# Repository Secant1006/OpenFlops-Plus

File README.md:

# OpenFlops-Plus
Enhanced version of open-source gotek

[OpenFlops](https://github.com/SukkoPera/OpenFlops)

[FlashFloppy](https://github.com/keirf/flashfloppy)

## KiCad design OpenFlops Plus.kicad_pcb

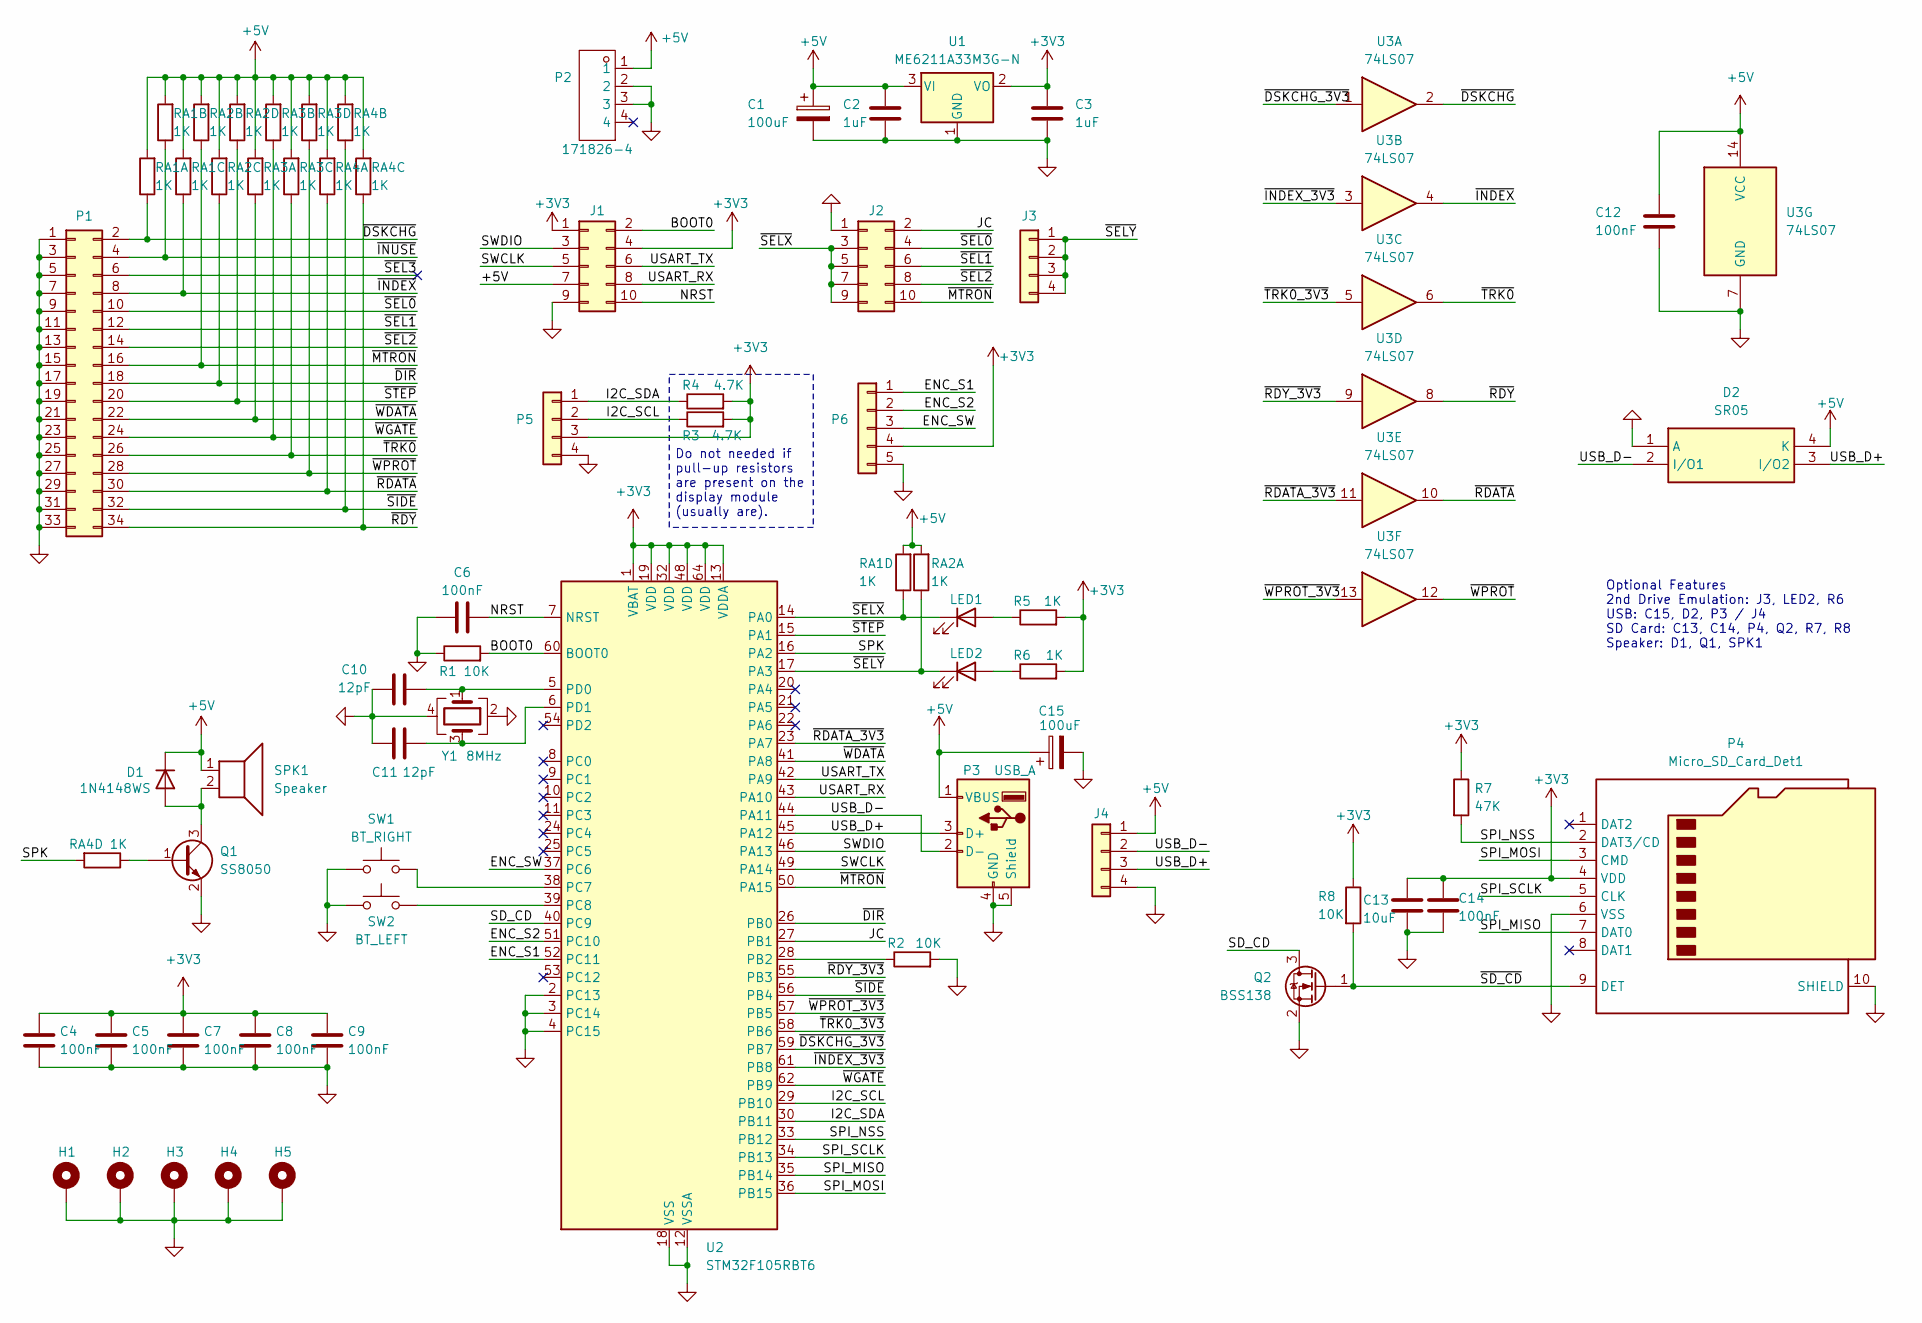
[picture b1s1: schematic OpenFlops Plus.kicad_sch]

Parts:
C1, C15: 100uF; CP_Radial_D6.3mm_P2.50mm
C2, C3: 1uF; C_0603_1608Metric
C4, C5, C6, C7, C8, C9, C12, C14: 100nF; C_0603_1608Metric
C10, C11: 12pF; C_0603_1608Metric
C13: 10uF; C_0805_2012Metric
D1: 1N4148WS; D_SOD-323
D2: SR05; SOT-143; Manufacturer_Part_Number SR05.TCT; Mouser Part Number 947-SR05.TCT
H1, H2, H3, H4, H5: MountingHole_Pad; MountingHole_3.2mm_M3_Pad
J1, J2: Conn_02x05_Odd_Even; PinHeader_2x05_P2.54mm_Vertical
J3, J4: Conn_01x04; PinHeader_1x04_P2.54mm_Vertical
LED1, LED2: LED; LED_D3.0mm
P1: Conn_02x17_Odd_Even; PinHeader_2x17_P2.54mm_Vertical
P2: 171826-4; CONN-TH_4P-P2.50_171826-4; Manufacturer Part 171826-4; LCSC Part Name 1x4P 间距:2.5mm 弯插
P3: USB_A; USB_A_Molex_67643_Horizontal
P4: Micro_SD_Card_Det1; TF-SMD_XKTF-015-N
P5: Conn_01x04; PinHeader_1x04_P2.54mm_Vertical
P6: Conn_01x05; PinHeader_1x05_P2.54mm_Vertical
Q1: SS8050; SOT-23
Q2: BSS138; SOT-23
R1, R2, R8: 10K; R_0603_1608Metric
R3, R4: 4.7K; R_0603_1608Metric
R5, R6: 1K; R_0603_1608Metric
R7: 47K; R_0603_1608Metric
RA1, RA2, RA3, RA4: 1K; R_Array_Convex_4x0603
SPK1: Speaker; Buzzer_12x9.5RM7.6
SW1: BT_RIGHT; SW_Tactile_SKHH_Angled
SW2: BT_LEFT; SW_Tactile_SKHH_Angled
U1: ME6211A33M3G-N; SOT-23-3
U2: STM32F105RBT6; LQFP-64_10x10mm_P0.5mm
U3: 74LS07; SOIC-14_3.9x8.7mm_P1.27mm
Y1: 8MHz; Crystal_SMD_3225-4Pin_3.2x2.5mm

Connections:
+3V3: C3.1, C4.1, C5.1, C7.1, C8.1, C9.1, C13.1, C14.1, J1.1, J1.4, P4.4 (VDD), P5.3, P6.4, R3.2, R4.2, R5.2, R6.2, R7.1, R8.1, U1.2 (VO), U2.1 (VBAT), U2.13 (VDDA), U2.19 (VDD), U2.32 (VDD), U2.48 (VDD), U2.64 (VDD)
+5V: C1.1, C2.1, C12.1, C15.1, D1.1 (K), D2.4 (K), J1.7, J4.1, P2.1, P3.1 (VBUS), RA1.5 (R4.2), RA1.6 (R3.2), RA1.7 (R2.2), RA1.8 (R1.2), RA2.5 (R4.2), RA2.6 (R3.2), RA2.7 (R2.2), RA2.8 (R1.2), RA3.5 (R4.2), RA3.6 (R3.2), RA3.7 (R2.2), RA3.8 (R1.2), RA4.6 (R3.2), RA4.7 (R2.2), RA4.8 (R1.2), SPK1.1, U1.3 (VI), U3.14 (VCC)
/BOOT0: J1.2, R1.2, U2.60 (BOOT0)
/ENC_S1: P6.1, U2.52 (PC11)
/ENC_S2: P6.2, U2.51 (PC10)
/ENC_SW: P6.3, U2.37 (PC6)
/I2C_SCL: P5.2, R3.1, U2.29 (PB10)
/I2C_SDA: P5.1, R4.1, U2.30 (PB11)
/JC: J2.2, U2.27 (PB1)
/NRST: C6.2, J1.10, U2.7 (NRST)
/SD_CD: Q2.3 (D), U2.40 (PC9)
/SPI_MISO: P4.7 (DAT0), U2.35 (PB14)
/SPI_MOSI: P4.3 (CMD), U2.36 (PB15)
/SPI_NSS: P4.2 (DAT3/CD), R7.2, U2.33 (PB12)
/SPI_SCLK: P4.5 (CLK), U2.34 (PB13)
/SPK: RA4.5 (R4.2), U2.16 (PA2)
/SWCLK: J1.5, U2.49 (PA14)
/SWDIO: J1.3, U2.46 (PA13)
/USART_RX: J1.8, U2.43 (PA10)
/USART_TX: J1.6, U2.42 (PA9)
/USB_D+: D2.3 (I/O2), J4.3, P3.3 (D+), U2.45 (PA12)
/USB_D-: D2.2 (I/O1), J4.2, P3.2 (D-), U2.44 (PA11)
/~DIR: P1.18, RA2.3 (R3.1), U2.26 (PB0)
/~DSKCHG_3V3: U2.59 (PB7), U3.1
/~DSKCHG: P1.2, RA1.1 (R1.1), U3.2
/~INDEX_3V3: U2.61 (PB8), U3.3
/~INDEX: P1.8, RA1.3 (R3.1), U3.4
/~INUSE: P1.4, RA1.2 (R2.1)
/~MTRON: J2.10, P1.16, RA2.2 (R2.1), U2.50 (PA15)
/~RDATA_3V3: U2.23 (PA7), U3.11
/~RDATA: P1.30, RA4.1 (R1.1), U3.10
/~RDY_3V3: U2.55 (PB3), U3.9
/~RDY: P1.34, RA4.3 (R3.1), U3.8
/~SD_CD: P4.9 (DET), Q2.1 (G), R8.2
/~SEL0: J2.4, P1.10
/~SEL1: J2.6, P1.12
/~SEL2: J2.8, P1.14
/~SEL3: P1.6
/~SELX: J2.3, J2.5, J2.7, J2.9, LED1.1 (K), RA1.4 (R4.1), U2.14 (PA0)
/~SELY: J3.1, J3.2, J3.3, J3.4, LED2.1 (K), RA2.1 (R1.1), U2.17 (PA3)
/~SIDE: P1.32, RA4.2 (R2.1), U2.56 (PB4)
/~STEP: P1.20, RA2.4 (R4.1), U2.15 (PA1)
/~TRK0_3V3: U2.58 (PB6), U3.5
/~TRK0: P1.26, RA3.3 (R3.1), U3.6
/~WDATA: P1.22, RA3.1 (R1.1), U2.41 (PA8)
/~WGATE: P1.24, RA3.2 (R2.1), U2.62 (PB9)
/~WPROT_3V3: U2.57 (PB5), U3.13
/~WPROT: P1.28, RA3.4 (R4.1), U3.12
GND: C1.2, C2.2, C3.2, C4.2, C5.2, C6.1, C7.2, C8.2, C9.2, C10.1, C11.1, C12.2, C13.2, C14.2, C15.2, D2.1 (A), H1.1, H2.1, H3.1, H4.1, H5.1, J1.9, J2.1, J4.4, P1.1, P1.3, P1.5, P1.7, P1.9, P1.11, P1.13, P1.15, P1.17, P1.19, P1.21, P1.23, P1.25, P1.27, P1.29, P1.31, P1.33, P2.2, P2.3, P3.4 (GND), P3.5 (Shield), P4.6 (VSS), P4.10 (SHIELD), P4.11, P4.12, P4.13, P5.4, P6.5, Q1.2 (E), Q2.2 (S), R1.1, R2.2, SW1.2, SW2.1, U1.1 (GND), U2.2 (PC13), U2.3 (PC14), U2.4 (PC15), U2.12 (VSSA), U2.18 (VSS), U2.31 (VSS), U2.47 (VSS), U2.63 (VSS), U3.7 (GND), Y1.2, Y1.4
unnamed: D1.2 (A), Q1.3 (C), SPK1.2
unnamed: LED1.2 (A), R5.1
unnamed: LED2.2 (A), R6.1
unnamed: Q1.1 (B), RA4.4 (R4.1)
unnamed: R2.1, U2.28 (PB2)
unnamed: SW1.1, U2.38 (PC7)
unnamed: SW2.2, U2.39 (PC8)
unnamed: C10.2, U2.5 (PD0), Y1.1
unnamed: C11.2, U2.6 (PD1), Y1.3

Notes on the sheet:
Do not needed if pull-up resistors are present on the display module (usually are).
Optional Features 2nd Drive Emulation: J3, LED2, R6 USB: C15, D2, P3 / J4 SD Card: C13, C14, P4, Q2, R7, R8 Speaker: D1, Q1, SPK1

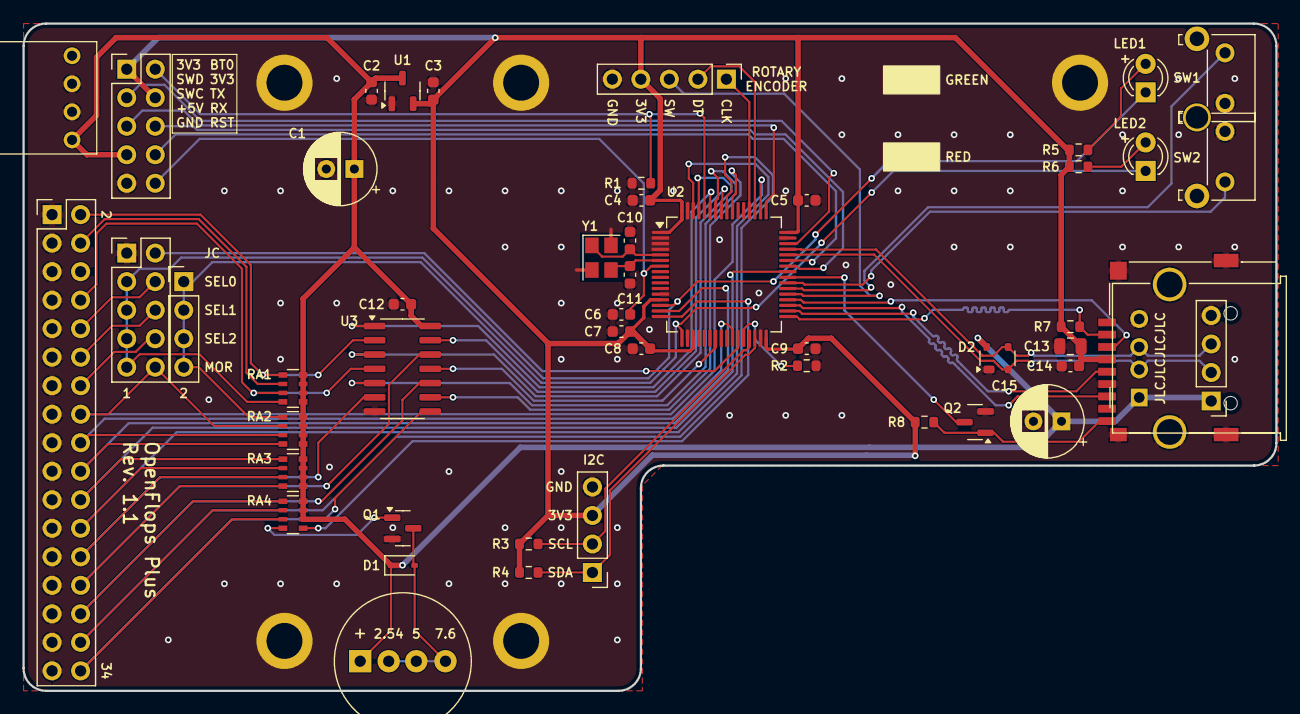
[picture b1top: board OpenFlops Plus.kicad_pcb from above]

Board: 2 copper layers, 111.6 x 59.4 mm, 55 parts (0 on the bottom side), 57 nets.

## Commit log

2026-05-26 Release 1.0
2026-06-17 Add PMOS for card reader
2026-06-21 Move to 74LS07
2026-06-22 Use SPI to manipulate SD card
2026-06-24 Update screen module
